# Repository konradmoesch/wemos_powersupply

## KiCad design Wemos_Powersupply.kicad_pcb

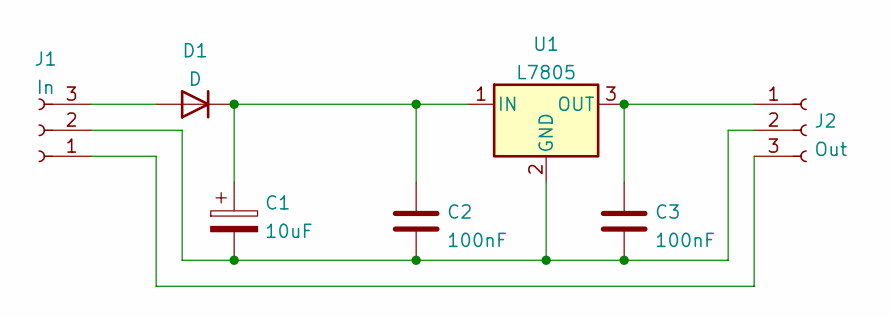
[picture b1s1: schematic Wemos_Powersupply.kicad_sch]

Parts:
C1: 10uF; CP_Radial_D5.0mm_P2.00mm
C2, C3: 100nF; C_Disc_D5.1mm_W3.2mm_P5.00mm
D1: D; D_DO-41_SOD81_P7.62mm_Horizontal
J1: In; PinSocket_1x03_P2.54mm_Vertical
J2: Out; PinSocket_1x03_P2.54mm_Vertical
U1: L7805; TO-220-3_Vertical

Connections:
unnamed: C3.1, J2.1, U1.3 (OUT)
unnamed: J1.1, J2.3
unnamed: C1.2, C2.2, C3.2, J1.2, J2.2, U1.2 (GND)
unnamed: D1.2 (A), J1.3
unnamed: C1.1, C2.1, D1.1 (K), U1.1 (IN)

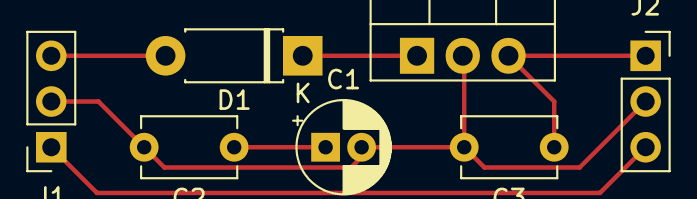
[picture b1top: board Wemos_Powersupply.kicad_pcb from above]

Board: 2 copper layers, 7 parts (0 on the bottom side), 5 nets.

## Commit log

2022-10-14 Add files
